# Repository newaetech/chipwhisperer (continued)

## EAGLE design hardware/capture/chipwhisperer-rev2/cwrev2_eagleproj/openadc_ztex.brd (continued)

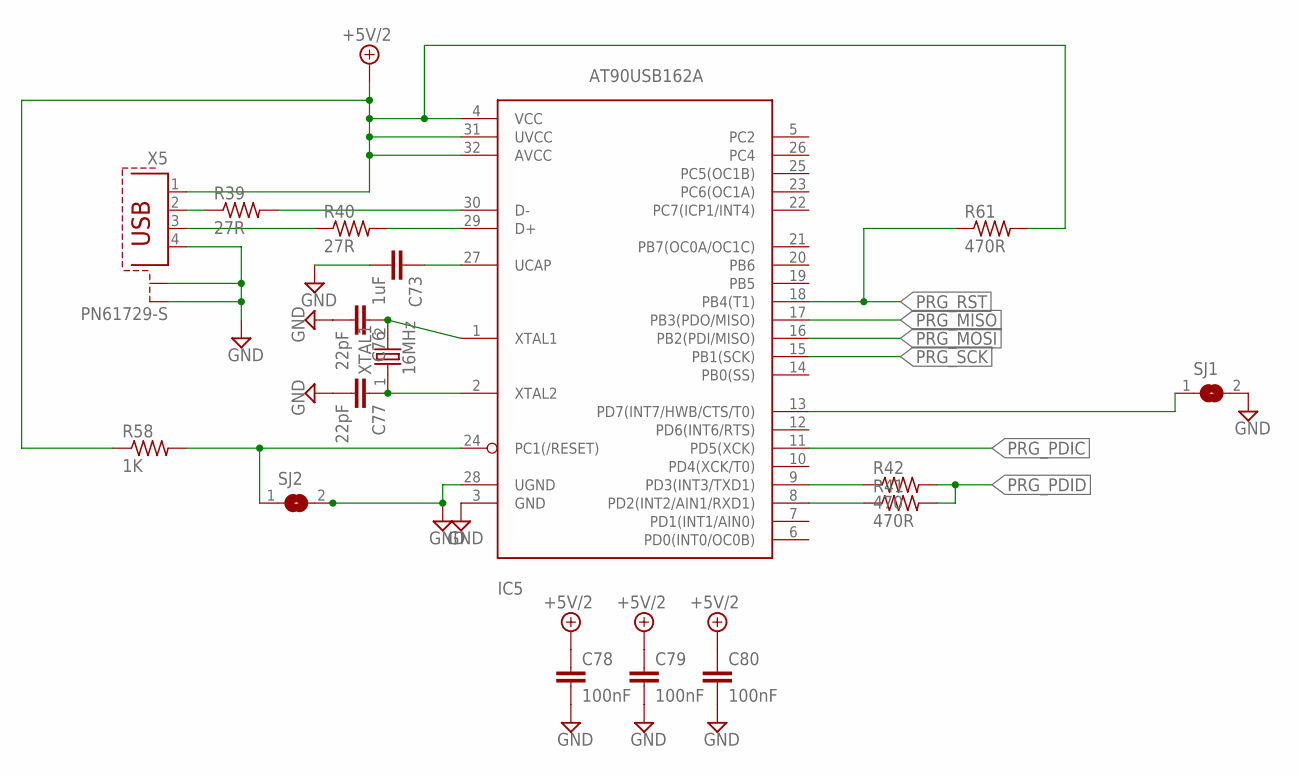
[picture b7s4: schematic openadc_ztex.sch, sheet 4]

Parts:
C73: 1uF; C0603
C76, C77: 22pF; C0603
C78, C79, C80: 100nF; C0603
IC5: AT90USB162A; TQFP32-08
R39, R40: 27R; R0603
R41, R61: 470R; R0603
R42: 470; R0603
R58: 1K; R0603
SJ1, SJ2: SJ
X5: PN61729-S
XTAL1: 16MHz; HC-49U

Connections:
+5V/2: C78.1, C79.1, C80.1, IC5.4 (VCC), IC5.31 (UVCC), IC5.32 (AVCC), R58.1, R61.2, X5.1; also elsewhere on the board
GND: C73.2, C76.2, C77.2, C78.2, C79.2, C80.2, IC5.3 (GND), IC5.28 (UGND), SJ1.2, SJ2.2, X5.4, X5.S1, X5.S2; also elsewhere on the board
unnamed: IC5.30 (D-), R39.2
unnamed: IC5.29 (D+), R40.2
unnamed: R40.1, X5.3
unnamed: R39.1, X5.2
unnamed: IC5.9 (PD3(INT3/TXD1)), R42.1
unnamed: C73.1, IC5.27 (UCAP)
unnamed: IC5.8 (PD2(INT2/AIN1/RXD1)), R41.1
unnamed: C76.1, IC5.1 (XTAL1), XTAL1.2
unnamed: C77.1, IC5.2 (XTAL2), XTAL1.1
unnamed: IC5.13 (PD7(INT7/HWB/CTS/T0)), SJ1.1
unnamed: IC5.24 (PC1(/RESET)), R58.2, SJ2.1
PRG_MISO: IC5.17 (PB3(PDO/MISO)); also elsewhere on the board
PRG_MOSI: IC5.16 (PB2(PDI/MISO)); also elsewhere on the board
PRG_PDIC: IC5.11 (PD5(XCK)); also elsewhere on the board
PRG_PDID: R41.2, R42.2; also elsewhere on the board
PRG_RST: IC5.18 (PB4(T1)), R61.1; also elsewhere on the board
PRG_SCK: IC5.15 (PB1(SCK)); also elsewhere on the board

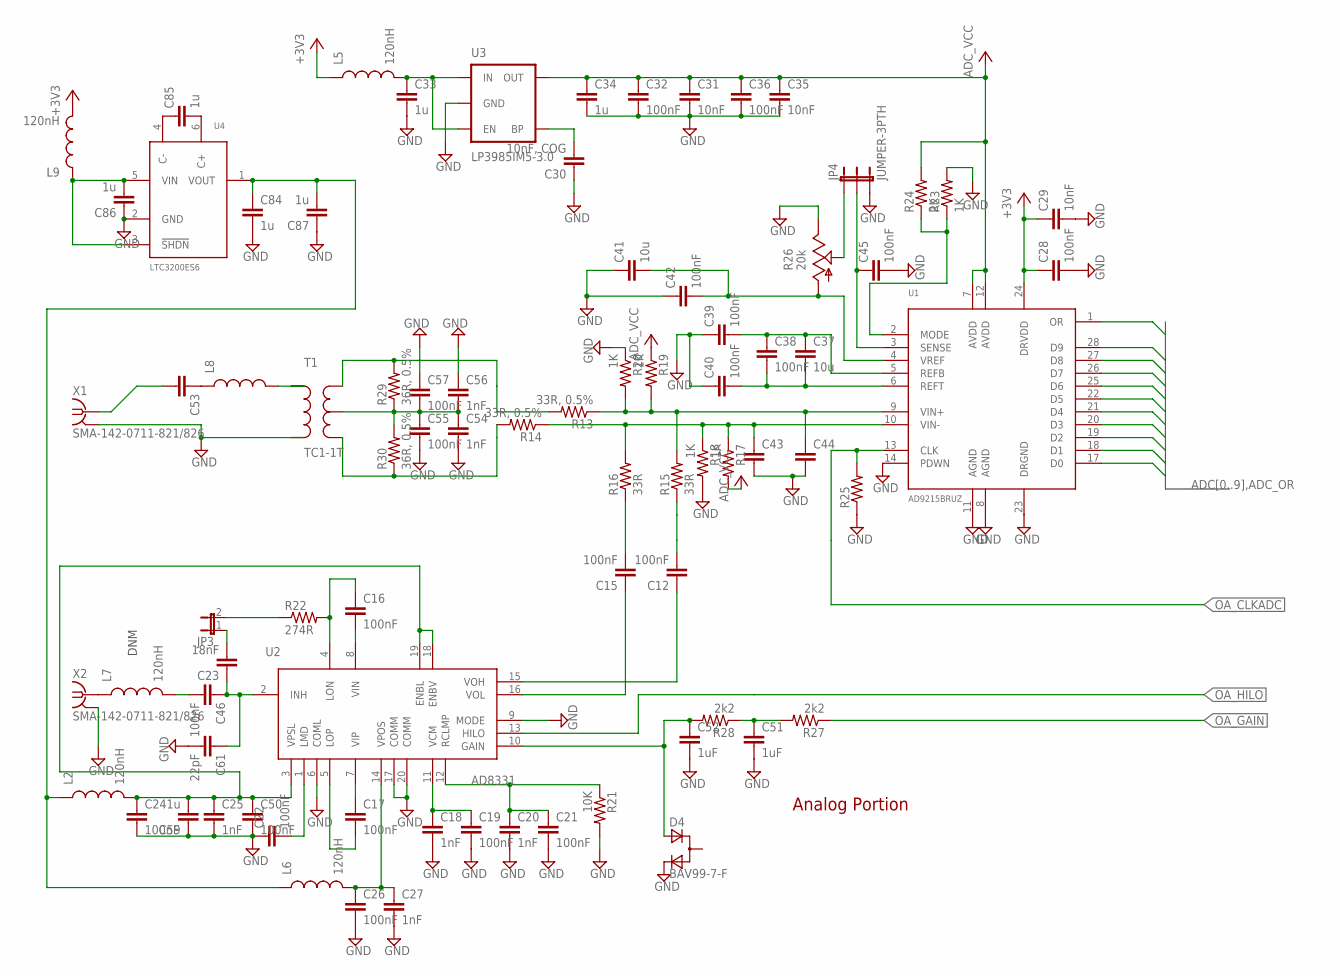
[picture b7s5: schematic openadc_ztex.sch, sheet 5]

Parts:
C12, C15, C46: 100nF; C0603K
C16, C17: 100nF; C0402
C18, C20, C25, C27, C54, C56: 1nF; C0402; PART# C1005X7R1E102K; DIGIKEY# 445-4924-1-ND
C19, C21, C22, C24, C26, C28, C32, C36, C38, C39, C40, C42, C45, C50, C55, C57: 100nF; C0402; PART# GRM155R61A104KA01D; DIGIKEY# 490-1318-1-ND
C23: 18nF; C0603; DIGIKEY# 587-1099-1-ND
C29: 10nF; C0402; DIGIKEY# 490-1312-1-ND
C30: 10nF, COG; C0402; DIGIKEY# 445-2664-1-ND
C31, C35: 10nF; C0402; PART# GRM155R71E103KA01D; DIGIKEY# 490-1312-1-ND
C33, C34, C84, C85, C86, C87: 1u; C0603; PART# GRM188R61A105KA61D; DIGIKEY# 490-1543-1-ND
C37: 10u; C0603; DIGIKEY# C1608X5R0J106K
C41: 10u; C0603
C43, C44: C-EUC0402; C0402
C51, C52: 1uF; C0603
C53: C-EUC0603K; C0603K
C59: 1u; C0402; PART# GRM188R61A105KA61D; DIGIKEY# 490-1543-1-ND
C61: 22pF; C0603; DIGIKEY# 587-1099-1-ND
D4: BAV99-7-F; SOT-23
JP3: JUMPER-2SMD-NC; SJ_2S
JP4: JUMPER-3PTH; 1X03
L2: 120nH; 0603; PART# MLF1608DR12M; DIGIKEY# 445-6234-1-ND
L5, L6, L7, L9: 120nH; 0603
L8: INDUCTOR0603; 0603
R13: 33R, 0.5%; R0603; DIGIKEY# RR08Q33DCT-ND
R14: 33R, 0.5%; R0603
R15, R16: 33R; R0603
R17: 1K; R0402; DIGIKEY# RHM1.00KCDCT-ND
R18, R19, R20, R23: 1K; R0402
R21: 10K; R0603
R22: 274R; R0603; DIGIKEY# RR08P274DCT-ND
R24: 2K; R0603
R25: R-US_R0603; R0603
R26: 20k; 3361P; PART# 3361P-1-203GLF; DIGIKEY# 3361P-203GLFCT-ND
R27, R28: 2k2; R0603
R29, R30: 36R, 0.5%; R0603; DIGIKEY# RR08Q36DCT-ND
T1: TC1-1T; AT224-1A
U1: AD9215BRUZ; TSSOP28; DIGIKEY# AD9215BRUZ-105-ND
U2: AD8331; QSOP20; PART# AD8331ARQZ; DIGIKEY# AD8331ARQZ-ND
U3: LP3985IM5-3.0; SOT23-5; DIGIKEY# LP3985IM5-3.0CT-ND
U4: LTC3200ES6; SOT23-6L
X1, X2: SMA-142-0711-821/826; J502-ND-142-0711-821/826

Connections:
+3V3: C28.1, C29.1, L5.1, L9.2, U1.24 (DRVDD); also elsewhere on the board
ADC_VCC: C31.1, C32.1, C34.1, C35.1, C36.1, R17.2, R19.1, R24.2, U1.7 (AVDD), U1.12 (AVDD), U3.5 (OUT)
GND: C18.2, C19.2, C20.2, C21.2, C22.1, C24.2, C25.2, C26.2, C27.2, C28.2, C29.2, C30.1, C31.2, C32.2, C33.2, C34.2, C35.2, C36.2, C39.1, C40.1, C41.1, C42.1, C43.2, C44.2, C45.2, C50.2, C51.2, C52.2, C54.2, C55.2, C56.1, C57.1, C59.1, C61.2, C84.2, C86.1, C87.1, D4.2 (C), JP4.3, R18.2, R20.1, R21.2, R23.2, R25.1, R26.1 (E), T1.4 (P2), U1.8 (AGND), U1.11 (AGND), U1.14 (PDWN), U1.23 (DRGND), U2.6 (COML), U2.9 (MODE), U2.17 (COMM), U2.20 (COMM), U3.2 (GND), U4.2 (GND), X1.G@1 (2), X1.G@2 (2), X1.G@3 (2), X1.G@4 (2), X2.G@1 (2), X2.G@2 (2), X2.G@3 (2), X2.G@4 (2); also elsewhere on the board
unnamed: C44.1, R13.1, R15.2, R19.2, R20.2, U1.9 (VIN+)
unnamed: C12.2, R15.1
unnamed: C15.2, R16.1
unnamed: C15.1, U2.16 (VOL)
unnamed: C12.1, U2.15 (VOH)
unnamed: C17.2, U2.5 (LOP)
unnamed: C17.1, U2.7 (VIP)
unnamed: C16.2, U2.8 (VIN)
unnamed: C16.1, R22.2, U2.4 (LON)
unnamed: C18.1, C19.1, U2.11 (VCM)
unnamed: C20.1, C21.1, R21.1, U2.12 (RCLMP)
unnamed: C22.2, U2.1 (LMD)
unnamed: C23.1, C46.1, C61.1, U2.2 (INH)
unnamed: C23.2, JP3.1
unnamed: JP3.2, R22.1
unnamed: C26.1, C27.1, L6.2, U2.14 (VPOS)
unnamed: C30.2, U3.4 (BP)
unnamed: C33.1, L5.2, U3.1 (IN), U3.3 (EN)
unnamed: C37.1, C38.1, C39.2, U1.5 (REFB)
unnamed: C37.2, C38.2, C40.2, U1.6 (REFT)
unnamed: C41.2, C42.2, R26.3 (A), U1.4 (VREF)
unnamed: C45.1, JP4.2, U1.3 (SENSE)
unnamed: R23.1, R24.1, U1.2 (MODE)
unnamed: C43.1, R14.1, R16.2, R17.1, R18.1, U1.10 (VIN-)
unnamed: JP4.1, R26.2 (S)
unnamed: L7.1, X2.1
unnamed: C51.1, R27.2, R28.1
unnamed: C52.1, D4.3 (A), R28.2, U2.10 (GAIN)
unnamed: C24.1, C25.1, C50.1, C59.2, L2.2, U2.3 (VPSL), U2.18 (ENBV), U2.19 (ENBL)
unnamed: R14.2, R30.1, T1.3 (S2)
unnamed: C53.2, X1.1
unnamed: C53.1, L8.1
unnamed: L8.2, T1.6 (P1)
unnamed: C85.1, U4.4 (C-)
unnamed: R13.2, R29.2, T1.1 (S1)
unnamed: C54.1, C55.1, C56.2, C57.2, R29.1, R30.2, T1.2 (ST)
unnamed: C46.2, L7.2
unnamed: C85.2, U4.6 (C+)
unnamed: C86.2, L9.1, U4.3 (!SHDN), U4.5 (VIN)
unnamed: C84.1, C87.2, L2.1, L6.1, U4.1 (VOUT)
OA_ADC0: U1.17 (D0); also elsewhere on the board
OA_ADC1: U1.18 (D1); also elsewhere on the board
OA_ADC2: U1.19 (D2); also elsewhere on the board
OA_ADC3: U1.20 (D3); also elsewhere on the board
OA_ADC4: U1.21 (D4); also elsewhere on the board
OA_ADC5: U1.22 (D5); also elsewhere on the board
OA_ADC6: U1.25 (D6); also elsewhere on the board
OA_ADC7: U1.26 (D7); also elsewhere on the board
OA_ADC8: U1.27 (D8); also elsewhere on the board
OA_ADC9: U1.28 (D9); also elsewhere on the board
OA_ADCOR: U1.1 (OR); also elsewhere on the board
OA_CLKADC: R25.2, U1.13 (CLK); also elsewhere on the board
OA_GAIN: R27.1; also elsewhere on the board
OA_HILO: U2.13 (HILO); also elsewhere on the board

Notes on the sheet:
Analog Portion
DNM

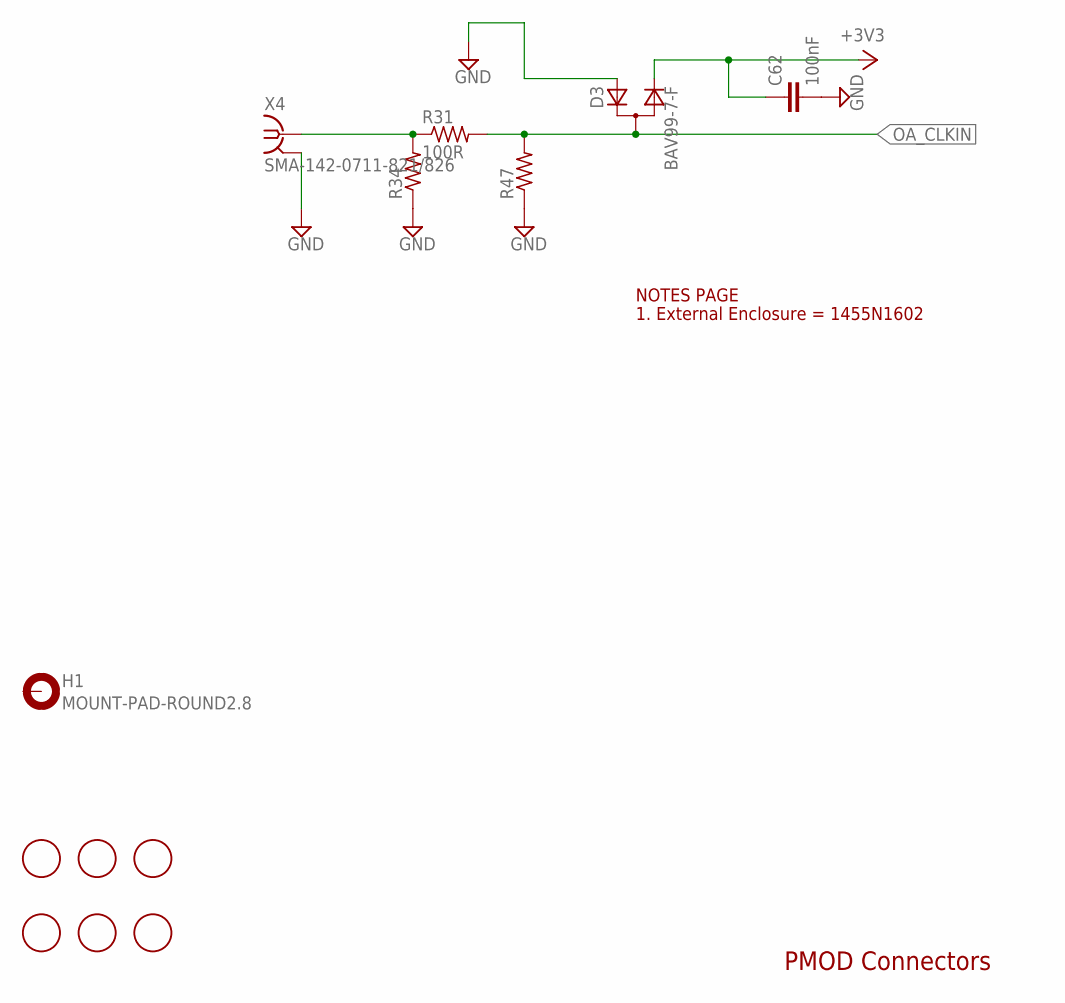
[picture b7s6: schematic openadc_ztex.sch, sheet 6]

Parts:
C62: 100nF; C0603
D3: BAV99-7-F; SOT-23
FID1, FID2, FID3, FID4, FID5, FID6: FIDUCIAL; FIDUCIAL_1MM
H1: MOUNT-PAD-ROUND2.8; 2,8-PAD
R31: 100R; R0805
R34, R47: R-US_R0805; R0805
X4: SMA-142-0711-821/826; J502-ND-142-0711-821/826

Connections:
+3V3: C62.1, D3.2 (C); also elsewhere on the board
GND: C62.2, D3.3 (A), R34.1, R47.1, X4.G@1 (2), X4.G@2 (2), X4.G@3 (2), X4.G@4 (2); also elsewhere on the board
unnamed: R31.1, R34.2, X4.1
OA_CLKIN: D3.1 (CA), R31.2, R47.2; also elsewhere on the board

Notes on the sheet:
PMOD Connectors
NOTES PAGE
1. External Enclosure = 1455N1602

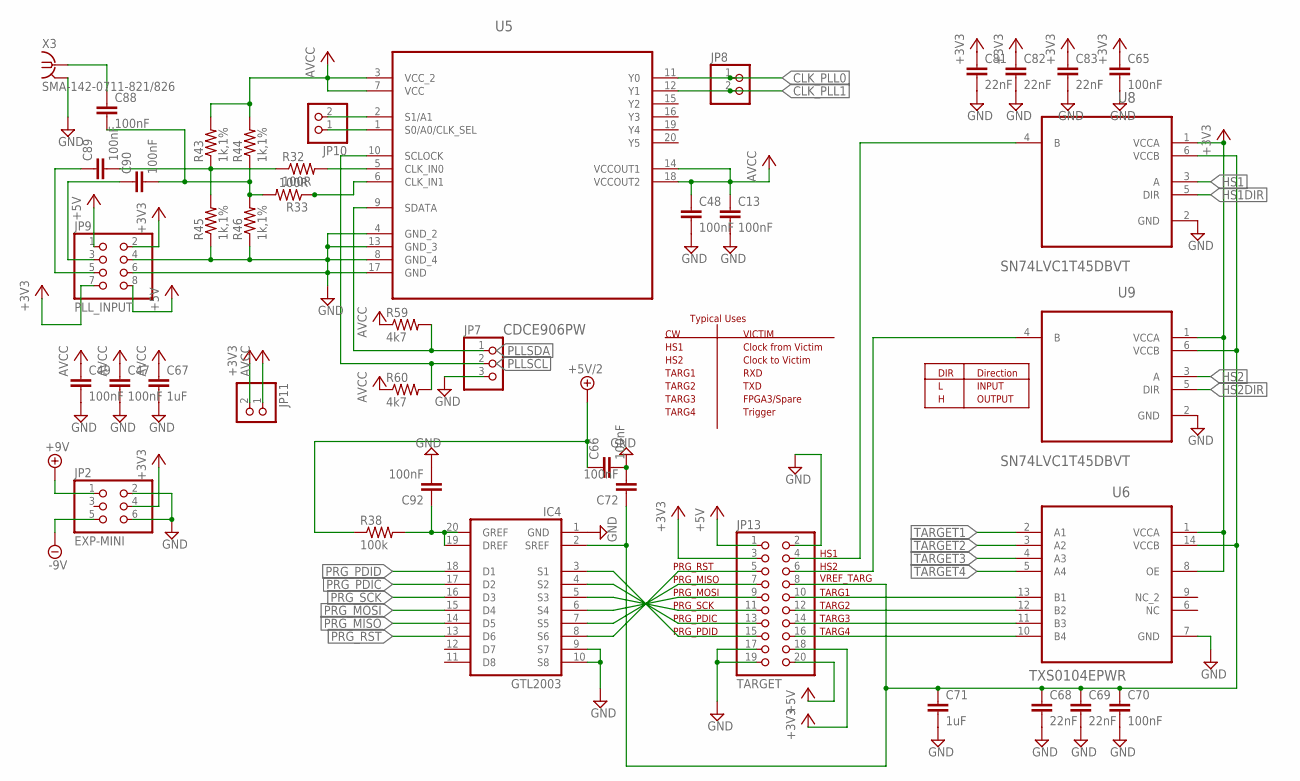
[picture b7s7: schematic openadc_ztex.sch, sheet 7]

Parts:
C13, C47, C48, C49, C65, C66, C70, C72, C88, C89, C90, C92: 100nF; C0603
C67, C71: 1uF; C0603
C68, C69, C81, C82, C83: 22nF; C0603
IC4: GTL2003; TSSOP20
JP2: EXP-MINI; 2X03/90
JP7: PINHD-1X3; 1X03
JP8, JP10, JP11: PINHD-1X2; 1X02
JP9: PLL_INPUT; 2X04/90
JP13: TARGET; 2X10/90
R32, R33: 100R; R0603
R38: 100k; R0603
R43, R44, R45, R46: 1k,1%; R0603
R59, R60: 4k7; R0603
U5: CDCE906PW; SOP65P640X120-20N
U6: TXS0104EPWR; SOP65P640X120-14N
U8, U9: SN74LVC1T45DBVT; SOT95P280X145-6N
X3: SMA-142-0711-821/826; J502-ND-142-0711-821/826

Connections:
+3V3: C65.1, C81.1, C82.1, C83.1, JP2.4, JP9.2, JP9.7, JP11.2, JP13.3, JP13.18, U6.1 (VCCA), U6.8 (OE), U8.1 (VCCA), U9.1 (VCCA); also elsewhere on the board
+5V: JP9.1, JP9.8, JP13.1, JP13.20; also elsewhere on the board
+5V/2: C66.1, R38.1; also elsewhere on the board
+9V: JP2.1; also elsewhere on the board
-9V: JP2.5; also elsewhere on the board
AVCC: C13.1, C47.1, C48.1, C49.1, C67.1, JP11.1, R43.2, R44.2, R59.1, R60.1, U5.3 (VCC_2), U5.7 (VCC), U5.14 (VCCOUT1), U5.18 (VCCOUT2)
CLK_PLL0: JP8.1, U5.11 (Y0); also elsewhere on the board
CLK_PLL1: JP8.2, U5.12 (Y1); also elsewhere on the board
GND: C13.2, C47.2, C48.2, C49.2, C65.2, C66.2, C67.2, C68.2, C69.2, C70.2, C71.2, C72.2, C81.2, C82.2, C83.2, C92.2, IC4.1 (GND), IC4.9 (S7), IC4.10 (S8), JP2.2, JP2.6, JP7.3, JP9.4, JP9.6, JP13.2, JP13.17, JP13.19, R45.1, R46.1, U5.4 (GND_2), U5.8 (GND_4), U5.13 (GND_3), U5.17 (GND), U6.7 (GND), U8.2 (GND), U9.2 (GND), X3.G@1 (2), X3.G@2 (2), X3.G@3 (2), X3.G@4 (2); also elsewhere on the board
HS1: U8.3 (A); also elsewhere on the board
HS1DIR: U8.5 (DIR); also elsewhere on the board
HS2: U9.3 (A); also elsewhere on the board
HS2DIR: U9.5 (DIR); also elsewhere on the board
unnamed: C89.1, JP9.5
unnamed: C90.1, JP9.3
unnamed: C89.2, R32.1, R43.1, R45.2
unnamed: C88.2, C90.2, R33.2, R44.1, R46.2
unnamed: C92.1, IC4.19 (DREF), IC4.20 (GREF), R38.2
unnamed: R33.1, U5.6 (CLK_IN1)
unnamed: IC4.8 (S6), JP13.5
unnamed: JP13.16, U6.10 (B4)
unnamed: JP13.14, U6.11 (B3)
unnamed: JP13.12, U6.12 (B2)
unnamed: JP13.10, U6.13 (B1)
unnamed: C68.1, C69.1, C70.1, C71.1, C72.1, IC4.2 (SREF), JP13.8, U6.14 (VCCB), U8.6 (VCCB), U9.6 (VCCB)
unnamed: IC4.7 (S5), JP13.7
unnamed: IC4.6 (S4), JP13.9
unnamed: IC4.5 (S3), JP13.11
unnamed: IC4.4 (S2), JP13.13
unnamed: IC4.3 (S1), JP13.15
unnamed: JP13.6, U9.4 (B)
unnamed: JP13.4, U8.4 (B)
unnamed: C88.1, X3.1
unnamed: JP10.2, U5.2 (S1/A1)
unnamed: JP10.1, U5.1 (S0/A0/CLK_SEL)
unnamed: R32.2, U5.5 (CLK_IN0)
PLLSCL: JP7.2, R60.2, U5.10 (SCLOCK); also elsewhere on the board
PLLSDA: JP7.1, R59.2, U5.9 (SDATA); also elsewhere on the board
PRG_MISO: IC4.14 (D5); also elsewhere on the board
PRG_MOSI: IC4.15 (D4); also elsewhere on the board
PRG_PDIC: IC4.17 (D2); also elsewhere on the board
PRG_PDID: IC4.18 (D1); also elsewhere on the board
PRG_RST: IC4.13 (D6); also elsewhere on the board
PRG_SCK: IC4.16 (D3); also elsewhere on the board
TARGET1: U6.2 (A1); also elsewhere on the board
TARGET2: U6.3 (A2); also elsewhere on the board
TARGET3: U6.4 (A3); also elsewhere on the board
TARGET4: U6.5 (A4); also elsewhere on the board

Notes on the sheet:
PRG_PDID
PRG_PDIC
PRG_SCK
PRG_MOSI
PRG_MISO
PRG_RST
HS2
HS1
TARG1
TARG2
TARG3
TARG4
VREF_TARG
VICTIM
Clock from Victim
Clock to Victim
RXD
TXD
FPGA3/Spare
Trigger
Typical Uses
DIR
OUTPUT
INPUT
Direction

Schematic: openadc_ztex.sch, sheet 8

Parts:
C91: C-EUC0603; C0603
CON6: USB-FPGA1.15
JP5: PINHD-2X15/90; 2X15/90
R35, R36: 2k2; R0603
U10: ATSHA204-SH; SO08

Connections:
+3V3: C91.1, JP5.3, R35.1, R36.1, U10.8 (VCC); also elsewhere on the board
+5V: JP5.1; also elsewhere on the board
EXPIO5: CON6.A27 (A27~C8~IO_L7N_0), JP5.5
EXPIO6: CON6.B26 (B26~B8~IO_L6P_0), JP5.6
EXPIO7: CON6.A26 (A26~A8~IO_L6N_0), JP5.7
EXPIO8: CON6.A25 (A25~D8~IO_L32N_0), JP5.8
EXPIO9: CON6.B25 (B25~D9~IO_L32P_0), JP5.9
EXPIO10: CON6.E25 (E25~C7~IO_L5P_0), JP5.10
EXPIO11: CON6.A24 (A24~C10~IO_L33N_0), JP5.11
EXPIO12: CON6.B24 (B24~D10~IO_L33P_0), JP5.12
EXPIO13: CON6.E24 (E24~C9~IO_L8P_0), JP5.13
EXPIO14: CON6.E23 (E23~B10~IO_L34P_GCLK19_0), JP5.14
EXPIO15: CON6.E22 (E22~A10~IO_L34N_GCLK18_0), JP5.15
EXPIO16: CON6.E21 (E21~D13~IO_L47P_0_NC45), JP5.16
EXPIO17: CON6.E20 (E20~D12~IO_L47N_0_NC45), JP5.17
EXPIO18: CON6.B20 (B20~F10~IO_L38P_0), JP5.18
EXPIO19: CON6.A20 (A20~C15~IO_L62P_0), JP5.19
EXPIO20: CON6.E19 (E19~A14~IO_L50N_0), JP5.20
EXPIO21: CON6.B19 (B19~D11~IO_L37P_GCLK13_0), JP5.21
EXPIO22: CON6.A19 (A19~C12~IO_L37N_GCLK12_0), JP5.22
EXPIO23: CON6.A18 (A18~C13~IO_L48P_0), JP5.23
EXPIO24: CON6.B18 (B18~A13~IO_L48N_0), JP5.24
EXPIO25: CON6.E18 (E18~B14~IO_L50P_0), JP5.25
EXPIO26: CON6.B17 (B17~C11~IO_L35P_GCLK17_0), JP5.26
EXPIO27: CON6.A17 (A17~A11~IO_L35N_GCLK16_0), JP5.27
EXPIO28: CON6.E17 (E17~A12~IO_L36N_GCLK14_0), JP5.28
GND: C91.2, JP5.2, JP5.4, JP5.29, JP5.30, U10.4 (GND); also elsewhere on the board
HS1: CON6.E14 (E14~B16~IO_L63P_SCP7_0); also elsewhere on the board
HS1DIR: CON6.A15 (A15~C14~IO_L46N_0); also elsewhere on the board
HS2: CON6.A14 (A14~A17~IO_L64N_SCP4_0); also elsewhere on the board
HS2DIR: CON6.B14 (B14~C17~IO_L64P_SCP5_0); also elsewhere on the board
unnamed: CON6.B28 (B28~D6~IO_L3P_0), R36.2, U10.6 (SCL)
unnamed: CON6.A28 (A28~C6~IO_L3N_0), R35.2, U10.5 (SDA)
PLLSCL: CON6.A29 (A29~A5~IO_L2N_0); also elsewhere on the board
PLLSDA: CON6.B29 (B29~C5~IO_L2P_0); also elsewhere on the board
TARGET1: CON6.E13 (E13~C16~IO_L65N_SCP2_0); also elsewhere on the board
TARGET2: CON6.A13 (A13~D17~IO_L65P_SCP3_0); also elsewhere on the board
TARGET3: CON6.B12 (B12~B18~IO_L66P_SCP1_0); also elsewhere on the board
TARGET4: CON6.A12 (A12~A18~IO_L66N_SCP0_0); also elsewhere on the board

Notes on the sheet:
A14
B14
C13
A13
D12
D11
C11
E11

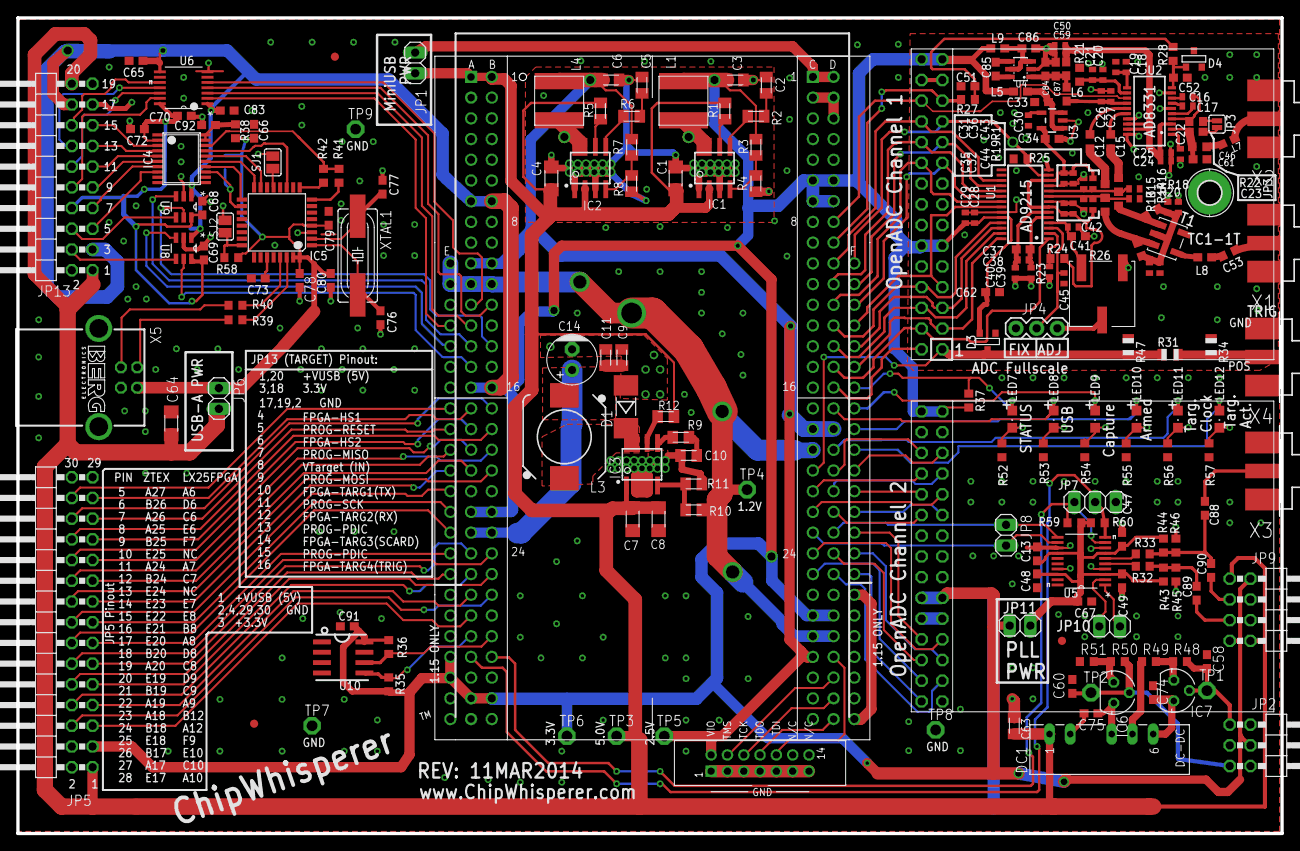
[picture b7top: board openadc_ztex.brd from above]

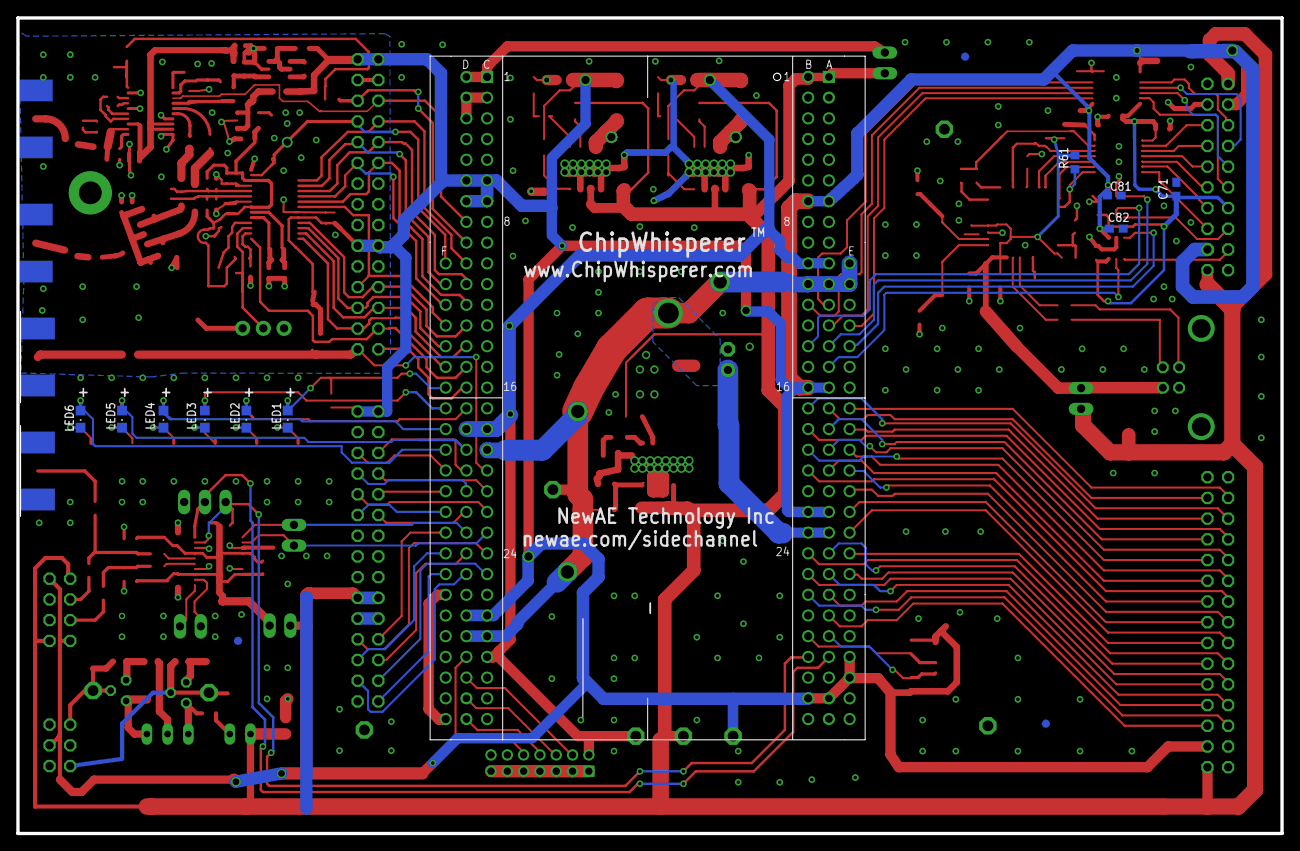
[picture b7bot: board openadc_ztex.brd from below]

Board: 2 copper layers, 155.0 x 100.0 mm, 235 parts (13 on the bottom side), 198 nets.

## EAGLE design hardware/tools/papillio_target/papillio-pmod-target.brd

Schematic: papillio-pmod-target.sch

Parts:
C1, C2, C3, C4, C5, C6, C7, C8: C-EUC0603; C0603
JP1: PINHD-2X6; 2X06
JP2, JP3: PINHD-1X4; 1X04
JP4: PINHD-2X10; 2X10
JP5, JP6: PINHD-2X3; 2X03
U1: TXS0104ED; SOIC127P600X175-14N
U2, U3: SN74LVC1T45DBVT; SOT95P280X145-6N

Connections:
+3V3: C1.1, C2.1, C3.1, C4.1, JP1.11, JP1.12, JP3.3, JP4.3, JP4.18, U1.1 (VCCA), U1.8 (OE), U2.1 (VCCA), U3.1 (VCCA)
+5V: JP3.4, JP4.1, JP4.20
GND: C1.2, C2.2, C3.2, C4.2, C5.2, C6.2, C7.2, C8.2, JP1.9, JP1.10, JP3.1, JP4.2, JP4.17, JP4.19, JP5.6, JP6.6, U1.7 (GND), U2.2 (GND), U3.2 (GND)
unnamed: JP1.2, JP2.1
unnamed: JP1.4, JP2.2, U2.5 (DIR)
unnamed: JP1.6, JP2.3, U3.3 (A)
unnamed: JP1.8, JP2.4, U2.3 (A)
unnamed: JP4.10, U1.10 (B4)
unnamed: JP4.16, U1.13 (B1)
unnamed: JP4.14, U1.12 (B2)
unnamed: JP4.12, U1.11 (B3)
unnamed: JP4.4, U3.4 (B)
unnamed: JP1.1, U1.5 (A4)
unnamed: JP1.3, U1.4 (A3)
unnamed: JP1.5, U1.3 (A2)
unnamed: JP1.7, U1.2 (A1)
unnamed: JP4.6, U2.4 (B)
unnamed: JP4.15, JP6.1
unnamed: JP4.13, JP6.5
unnamed: JP4.5, JP5.5
unnamed: JP4.11, JP5.3
unnamed: JP4.9, JP5.4
unnamed: JP4.7, JP5.1
VCCIO: C5.1, C6.1, C7.1, C8.1, JP4.8, JP5.2, JP6.2, U1.14 (VCCB), U2.6 (VCCB), U3.6 (VCCB)

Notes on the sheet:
PMOD
Papillio Power
TARG1
TARG2
TARG3
TARG4
VCC
MOSI
GND
RST
SCK
MISO
DATA
CLOCK

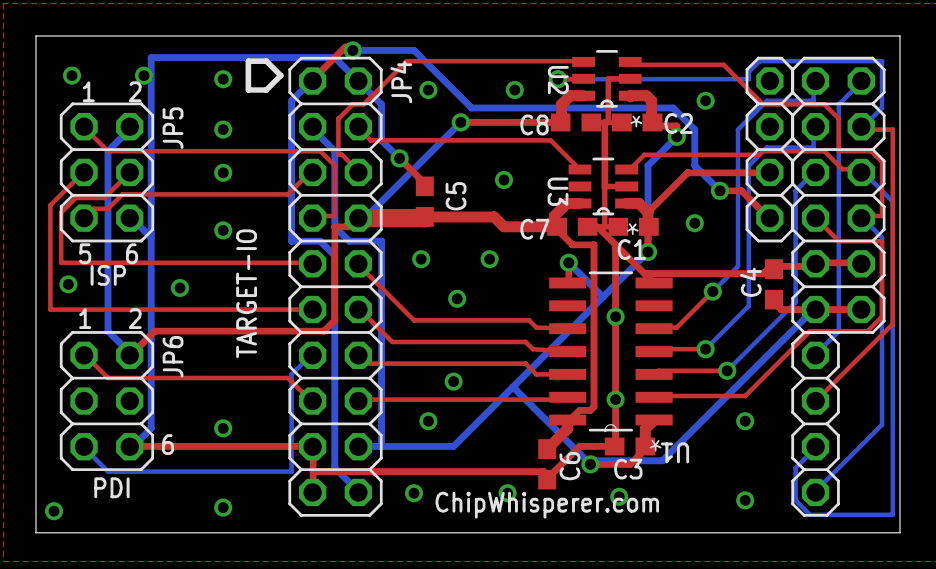
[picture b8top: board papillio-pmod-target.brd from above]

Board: 2 copper layers, 48.0 x 27.6 mm, 17 parts (0 on the bottom side), 24 nets.

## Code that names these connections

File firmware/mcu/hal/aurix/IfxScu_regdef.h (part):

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typedef struct _Ifx_SCU_IOCR_Bits
{
    unsigned int reserved_0:4;              /**< \brief \internal Reserved */
    unsigned int PC0:4;                     /**< \brief [7:4] Control for ESR Pin x (rw) */
    unsigned int reserved_8:4;              /**< \brief \internal Reserved */
    unsigned int PC1:4;                     /**< \brief [15:12] Control for ESR Pin x (rw) */
    unsigned int reserved_16:16;            /**< \brief \internal Reserved */
} Ifx_SCU_IOCR_Bits;

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/** \\brief  ESR Pad Driver Mode Register */
typedef struct _Ifx_SCU_PDR_Bits
{
    unsigned int PD0:3;                     /**< \brief [2:0] Pad Driver Mode for ESR Pins 0 and 1 (rw) */
    unsigned int PL0:1;                     /**< \brief [3:3] Reserved in this product (rw) */
    unsigned int PD1:3;                     /**< \brief [6:4] Pad Driver Mode for ESR Pins 0 and 1 (rw) */
    unsigned int PL1:1;                     /**< \brief [7:7] Reserved in this product (rw) */
    unsigned int reserved_8:24;             /**< \brief \internal Reserved */
} Ifx_SCU_PDR_Bits;
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
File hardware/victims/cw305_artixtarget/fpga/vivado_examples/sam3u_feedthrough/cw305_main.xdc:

######## HARDWARE ON BOARD

#LEDs
set_property DRIVE 8 [get_ports led1]
set_property PACKAGE_PIN T2 [get_ports led1]

set_property DRIVE 8 [get_ports led2]
set_property PACKAGE_PIN T3 [get_ports led2]

set_property DRIVE 8 [get_ports led3]
set_property PACKAGE_PIN T4 [get_ports led3]

#Switch's
set_property PACKAGE_PIN J16 [get_ports j16_sel]
set_property PACKAGE_PIN K16 [get_ports k16_sel]
set_property PACKAGE_PIN L14 [get_ports l14_sel]
set_property PACKAGE_PIN K15 [get_ports k15_sel]
set_property PACKAGE_PIN R1 [get_ports pushbutton]

#PLL Connections
set_property PACKAGE_PIN N13 [get_ports pll_clk1]
#set_property PACKAGE_PIN E12 [get_ports pll_clk2]

######## 20-Pin Connector

set_property PACKAGE_PIN T14 [get_ports tio_trigger_out]

set_property PACKAGE_PIN M16 [get_ports tio_clkout]

set_property PACKAGE_PIN N14 [get_ports tio_clkin]

####### USB Connector: SAM3U interface

set_property PACKAGE_PIN F5 [get_ports usb_clk]

set_property IOSTANDARD LVCMOS33 [get_ports *]
set_property PACKAGE_PIN A7 [get_ports {sam3u_usb_data[0]}]
set_property PACKAGE_PIN B6 [get_ports {sam3u_usb_data[1]}]
set_property PACKAGE_PIN D3 [get_ports {sam3u_usb_data[2]}]
set_property PACKAGE_PIN E3 [get_ports {sam3u_usb_data[3]}]
set_property PACKAGE_PIN F3 [get_ports {sam3u_usb_data[4]}]
set_property PACKAGE_PIN B5 [get_ports {sam3u_usb_data[5]}]
set_property PACKAGE_PIN K1 [get_ports {sam3u_usb_data[6]}]
set_property PACKAGE_PIN K2 [get_ports {sam3u_usb_data[7]}]

set_property PACKAGE_PIN F4 [get_ports {sam3u_usb_addr[0]}]
set_property PACKAGE_PIN G5 [get_ports {sam3u_usb_addr[1]}]
set_property PACKAGE_PIN J1 [get_ports {sam3u_usb_addr[2]}]
set_property PACKAGE_PIN H1 [get_ports {sam3u_usb_addr[3]}]
set_property PACKAGE_PIN H2 [get_ports {sam3u_usb_addr[4]}]
set_property PACKAGE_PIN G1 [get_ports {sam3u_usb_addr[5]}]
set_property PACKAGE_PIN G2 [get_ports {sam3u_usb_addr[6]}]
set_property PACKAGE_PIN F2 [get_ports {sam3u_usb_addr[7]}]
set_property PACKAGE_PIN E1 [get_ports {sam3u_usb_addr[8]}]
set_property PACKAGE_PIN E2 [get_ports {sam3u_usb_addr[9]}]
set_property PACKAGE_PIN D1 [get_ports {sam3u_usb_addr[10]}]

set_property PACKAGE_PIN A4 [get_ports sam3u_usb_rdn]
set_property PACKAGE_PIN C2 [get_ports sam3u_usb_wrn]
set_property PACKAGE_PIN A3 [get_ports sam3u_usb_cen]

#set_property PACKAGE_PIN A5 [get_ports sam3u_usb_trigger]

####### target USB interface (40-pin header, JP3)
# count | header pin # | PCB name  | FPGA pin
# ------+--------------+-----------+---------
#  0    |          5   |       IO5 | A12
#  1    |          6   |       IO6 | B12
#  2    |          7   |       IO7 | A14
#  3    |          8   |       IO8 | A13
#  4    |          9   |       IO9 | A15
#  5    |         10   |      IO10 | B15
#  6    |         11   |      IO11 | C12
#  7    |         12   |      IO12 | C11
#  8    |         13   |      IO13 | B14
#  9    |         14   |      IO14 | C14
# 10    |         15   |      IO15 | B16
# 11    |         16   |      IO16 | C16
# 12    |         17   |      IO17 | C13
# 13    |         18   |      IO18 | D13
# 14    |         23   |      IO23 | D15
# 15    |         24   |      IO24 | D14
# 16    |         25   |      IO25 | E15
# 17    |         26   |      IO26 | D16
# 18    |         27   |      IO27 | E13
# 19    |         28   |      IO28 | E16
# 20    |         29   |      IO29 | F15
# 21    |         30   |      IO30 | F12
# 22    |         31   |      IO31 | E11
# 23    |         32   |      IO32 | F13
# ------+--------------+-----------+---------
# 24    |         33   |      TIO4 | T14
# 25    |         34   |    EMCCLK | M15
# 26    |         37   |     IOD_P | H16
# 27    |         38   |     IOD_N | G16

# physical arrangement:
# header pin # | PCB name  | FPGA pin | header pin # | PCB name  | FPGA pin | 
# -------------+-----------+----------+--------------+-----------+----------+-
#          5   |       IO5 | A12      |          6   |       IO6 | B12      |
#          7   |       IO7 | A14      |          8   |       IO8 | A13      |
#          9   |       IO9 | A15      |         10   |      IO10 | B15      |
#         11   |      IO11 | C12      |         12   |      IO12 | C11      |
#         13   |      IO13 | B14      |         14   |      IO14 | C14      |
#         15   |      IO15 | B16      |         16   |      IO16 | C16      |
#         17   |      IO17 | C13      |         18   |      IO18 | D13      |
# -------------+-----------+----------+--------------+-----------+----------+-
#         NC   |        NC | NC       |         NC   |        NC | NC       | 
#         NC   |        NC | NC       |         NC   |        NC | NC       | 
# -------------+-----------+----------+--------------+-----------+----------+-
#         23   |      IO23 | D15      |         24   |      IO24 | D14      |
#         25   |      IO25 | E15      |         26   |      IO26 | D16      |
#         27   |      IO27 | E13      |         28   |      IO28 | E16      |
#         29   |      IO29 | F15      |         30   |      IO30 | F12      |
#         31   |      IO31 | E11      |         32   |      IO32 | F13      |
# -------------+-----------+----------+--------------+-----------+----------+-


# to Genesys2 JB:
set_property PACKAGE_PIN A12 [get_ports {ext_usb_data[3]}]
set_property PACKAGE_PIN A14 [get_ports {ext_usb_data[2]}]
set_property PACKAGE_PIN A15 [get_ports {ext_usb_data[1]}]
set_property PACKAGE_PIN C12 [get_ports {ext_usb_data[0]}]

set_property PACKAGE_PIN B12 [get_ports {ext_usb_data[7]}]
set_property PACKAGE_PIN A13 [get_ports {ext_usb_data[6]}]
set_property PACKAGE_PIN B15 [get_ports {ext_usb_data[5]}]
set_property PACKAGE_PIN C11 [get_ports {ext_usb_data[4]}]

# to Genesys2 JA:
set_property PACKAGE_PIN D15 [get_ports {ext_usb_wrn }]
set_property PACKAGE_PIN E15 [get_ports {ext_usb_rdn }]
set_property PACKAGE_PIN E13 [get_ports {ext_usb_cen }]
set_property PACKAGE_PIN F15 [get_ports {ext_usb_clk }]

set_property PACKAGE_PIN D14 [get_ports {ext_usb_addr[10]}]
set_property PACKAGE_PIN D16 [get_ports {ext_usb_addr[9]}]
set_property PACKAGE_PIN E16 [get_ports {ext_usb_addr[8]}]
set_property PACKAGE_PIN F12 [get_ports {ext_usb_addr[7]}]

# between JA/JB, to Genesys2 JC:
set_property PACKAGE_PIN B14 [get_ports {ext_usb_addr[0]}]; # white
set_property PACKAGE_PIN B16 [get_ports {ext_usb_addr[1]}]; # red
set_property PACKAGE_PIN C13 [get_ports {ext_usb_addr[2]}]; # yellow

set_property PACKAGE_PIN C14 [get_ports {ext_usb_addr[3]}]; # black
set_property PACKAGE_PIN C16 [get_ports {ext_usb_addr[4]}]; # green
set_property PACKAGE_PIN D13 [get_ports {ext_usb_addr[5]}]; # blue

set_property PACKAGE_PIN E11 [get_ports {ext_usb_addr[6]}];      # white
set_property PACKAGE_PIN F13 [get_ports {ext_tio_trigger_in}];   # yellow


create_clock -period 10.000 -name usb_clk -waveform {0.000 5.000} [get_nets usb_clk]
create_clock -period 10.000 -name tio_clkin -waveform {0.000 5.000} [get_nets tio_clkin]
create_clock -period 10.000 -name pll_clk1 -waveform {0.000 5.000} [get_nets pll_clk1]

# both input clocks have same properties so there is no point in doing timing analysis for both:
set_case_analysis 1 [get_pins U_clocks/CCLK_MUX/S]

# No spec for these, seems sensible:
set_input_delay -clock usb_clk -add_delay 2.000 [get_ports sam3u_usb_addr]
set_input_delay -clock usb_clk -add_delay 2.000 [get_ports sam3u_usb_data]
#set_input_delay -clock usb_clk -add_delay 2.000 [get_ports sam3u_usb_trigger]
set_input_delay -clock usb_clk -add_delay 2.000 [get_ports sam3u_usb_cen]
set_input_delay -clock usb_clk -add_delay 2.000 [get_ports sam3u_usb_rdn]
set_input_delay -clock usb_clk -add_delay 2.000 [get_ports sam3u_usb_wrn]

set_input_delay -clock usb_clk -add_delay 0.000 [get_ports j16_sel]
set_input_delay -clock usb_clk -add_delay 0.000 [get_ports k16_sel]
set_input_delay -clock [get_clocks usb_clk] -add_delay 0.500 [get_ports pushbutton]

set_output_delay -clock usb_clk 0.000 [get_ports led1]
set_output_delay -clock usb_clk 0.000 [get_ports led2]
set_output_delay -clock usb_clk 0.000 [get_ports led3]
set_output_delay -clock usb_clk 0.000 [get_ports sam3u_usb_data]
set_output_delay -clock usb_clk 0.000 [get_ports tio_trigger_out]
set_output_delay -clock usb_clk 0.000 [get_ports tio_clkout]
set_false_path -to [get_ports led1]
set_false_path -to [get_ports led2]
set_false_path -to [get_ports led3]
set_false_path -to [get_ports sam3u_usb_data]
set_false_path -to [get_ports tio_trigger_out]
set_false_path -to [get_ports tio_clkout]

set_property CFGBVS VCCO [current_design]
set_property CONFIG_VOLTAGE 3.3 [current_design]

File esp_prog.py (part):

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scope = cw.scope()
scope.default_setup()
target = cw.target(scope)
scope.io.tio3 = 0
scope.io.pdic=0
scope.clock.clkgen_freq = 26E6
import time
scope.io.nrst = 0
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MAX_UINT24 = 0xffffff

DEFAULT_TIMEOUT = 3                   # timeout for most flash operations
START_FLASH_TIMEOUT = 20              # timeout for starting flash (may perform erase)
CHIP_ERASE_TIMEOUT = 120              # timeout for full chip erase
MAX_TIMEOUT = CHIP_ERASE_TIMEOUT * 2  # longest any command can run
SYNC_TIMEOUT = 0.1                    # timeout for syncing with bootloader
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
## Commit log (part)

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2023-07-13 CW340: add docstrings and jumper warning.
2023-07-13 appease mypy
2023-07-27 Husky triggering updates.
    1. Allow SAD to generate triggers when not armed (i.e. after the ADC
    capture is done).
    2. Retrieve timestamped trigger times (when using multiple triggers).
2023-07-27 Husky: automatically set ADC high/low speed mode.
    Previously it was always set to low speed mode; the datasheet recommends
    high speed mode when the sampling frequency is > 80 MHz; this is what we
    do now.
2023-07-27 Arm RSA WIP changes
2023-07-28 Update Husky FPGA bitfile: fix for https://github.com/newaetech/chipwhisperer-husky-fpga/issues/16
2023-08-01 revert back to original rsa arm code
2023-08-15 FPGA targets: move ss2 wrapper to fpga-common.
2023-08-15 Add SS2-style iCE40 AES FPGA target.
    This allows iCE40 to be treated as a pseudo-CW305 target (see CW305 AES
    notebook).
2023-08-15 update mac install instructions
2023-08-17 CW310: fix typo on current_vccint property
2023-08-17 Allow CW310/340 to use all CW305 properties.
2023-08-17 Add ext_offset[x] = y support for multiglitch
2023-08-17 remove print from MultiGlitchList
2023-08-22 Remove windows install section about make/compilers (always installed now)
2023-08-23 Update jupyter submodule
2023-08-26 Refactored vcc glitch mosfet control; Refactored default and glitch setup/disable API; Added message utilities; Added optimized data copy; Added API utilities and tests
2023-08-28 Add sequenced triggers for Husky.
2023-08-28 Husky USERIO: print info about each pin.
2023-08-28 make mypy happy
2023-08-29 Husky: expand num_triggers property.
2023-08-30 Tweaks towards supporting > 2 sequence triggers.
2023-09-01 Husky trig seq: option to make SAD always active.
2023-09-01 Husky: tweak USERIO fpga_mode signals
2023-09-05 test_husky.py: make test_pll smarter
2023-09-05 update virtual box instructions for potential USB issue
2023-09-05 Add target FW for trace-less uecc attack notebook.
2023-09-06 Update jupyter for uecc notebooks.
2023-09-06 Update Husky FPGA bitfile.
    Adds trigger timestamp and trigger sequencer features. Bitfile built
    from:
    https://github.com/newaetech/chipwhisperer-husky-fpga/commit/71dec210372a61f6cb1d9f99b23cbf440d9396ae
2023-09-06 Make sure np arrays used for clock calcs are int64
2023-09-10 Optimized GlitchController iterator and added utilites; Added glitch looper API; Added Simple Serial glitch looper test script
2023-09-12 add custom-firmware.rst
2023-09-12 Update side bar
2023-09-14 Don't check stm32fprog pins on Nano
2023-09-15 fix missing newline in docs
2023-09-15 Fix lite build
2023-09-20 Add usart capability to CW340
2023-09-21 Add multi usart to CW310/CW340
2023-09-25 Update Husky bitfiles, test script.
    Adds trigger sequencer.
2023-09-26 Husky: make default_setup() reset segments to 1
2023-10-01 Refactored GPIO API
2023-10-04 Fix https://github.com/newaetech/chipwhisperer/issues/463
2023-10-06 Add USART dependency for CW310
    The CW310 target currently is missing the USART dependency. This
    PR fixes the issue.
2023-10-09 [naeusb] Remove claimInterface
    Remove `self.handle.claimInterface(0)` to enable connection for CW305.
2023-10-10 Add getCWType to cw340
2023-10-12 Add missing properties to CW310.py
2023-10-16 Husky: fix https://github.com/newaetech/chipwhisperer-husky-fpga/issues/17 and add more testing around it.
2023-10-24 Allow to connect to Nano by name.
    (when multiple ChipWhisperers are connected)
2023-10-24 Fix missing arg in husky clock debug msg
2023-10-27 add nbstripout to install instructions
2023-10-31 Remove old FPGA target material.
2023-10-31 (re)-add fpga-common submodule
2023-10-31 Target FPGA: remove duplicate source files.
2023-11-01 Target FPGA: update generate_firmware_files.py
    (pull target FPGA bitfiles from their new locations)
2023-11-02 Jupyter update (sca204, Ibex)
2023-11-02 Add RTFM links to FPGA targets README.
2023-11-03 typo
2023-11-06 Documentation fixes.
2023-11-06 Fix footguns around hidden Husky stream properties
2023-11-14 Claim interface on Darwin
2023-11-19 FPGA register updates.
    Functionally equivalent. FPGA register address space was getting tight
    and so some were combined or eliminated. FPGA-side changes are:
    https://github.com/newaetech/chipwhisperer-husky-fpga/commit/7e0bec0497cc4ab0be0edc18e0264e9167e5a83e
2023-11-23 Husky: add "trigger too soon" error.
2023-11-23 FPGA targets: fix AES defines file.
    Name/location were wrong, due to recent target FPGA organizational
    changes.
2023-11-27 Make bits_per_sample Husky-only.
2024-01-02 Bump tj-actions/changed-files in /.github/workflows
    Bumps [tj-actions/changed-files](https://github.com/tj-actions/changed-files) from 29.0.1 to 41.0.0.
    - [Release notes](https://github.com/tj-actions/changed-files/releases)
    - [Changelog](https://github.com/tj-actions/changed-files/blob/main/HISTORY.md)
    - [Commits](https://github.com/tj-actions/changed-files/compare/v29.0.1...v41.0.0)
    ---
    updated-dependencies:
2024-01-15 Husky: update bitfile.
    From https://github.com/newaetech/chipwhisperer-husky-fpga/commit/e410ae83b16c6dcdb642a2ace36b3b21f1b53098
2024-02-02 Add glitch_plot_3d() for 3D plots
2024-02-24 Added reset of the scope's connection before closing it
2024-03-18 Update stm32f0_hal_nano.c
    Add functions led_ok_on() led_ok_off() led_error_on() and led_error_off() to be abe to control target leds from firmware
2024-03-19 Fix led_ok and led_error being ifdef'd out
2024-03-20 Fix typo? in scope-api
2024-03-20 Fix tracewhisperer docs
2024-03-30 make BAUD_RATE definable
2024-03-30 remove FOSC defines, make everything based on F_CPU
2024-03-30 fix cpu rate checking
2024-03-30 fix readme
2024-03-30 fix delay
2024-04-07 update documentation on target_pwr (disables some IO)
2024-04-11 Husky SAD updates WIP.
2024-04-15 Add xonxoff support
2024-04-15 Fix version for XONXOFF for CW310
2024-04-16 Make test_s6_glitch.py run again.
    WIP as current usefulness is low.
2024-04-17 Fix test_s6.py test script.
    Renamed from test_s6_glitch.py, because it now does more than glitch
    testing: it also checks the CW generated clock.
2024-04-17 Update Husky bitfile for https://github.com/newaetech/chipwhisperer/issues/481
2024-04-17 Remove double glitch warning.
    Well tested by tests/test_s6.py; confident that double glitches are no
    longer a thing.
2024-04-23 Add **kwargs to CDC
2024-04-23 Add XMEGA16D4 programming
2024-05-30 Add scope.glitch.mmcm_locked property Lite/Pro.
2024-05-31 Add parity and stopbits for serial
2024-06-18 glitch controller plot fixes, allow saving and loading of results
2024-06-25 Husky: have userio.drive_data return what was set.
2024-06-27 Fix for make 4.4+?
2024-07-15 Husky SAD: make reference setter friendlier.
    Accept more types as-is and translate as needed instead of requiring
    user to do so.
2024-08-08 Husky: fix scope.adc.errors reporting.
    'trigger too soon' and 'gain too low' were switched.
2024-08-09 Husky SAD: more error checking.
2024-08-13 Add delay to default_setup() for clocks to settle.
    On CW-lite, calling default_setup() after connecting caused
    scope.clock.adc_freq to read and cache the clock frequency before it's
    settled (even if scope.clock.adc_locked is True). A small delay seems
    like the best fix.
2024-08-13 move mcu firmware to firmware/mcu
2024-08-14 remove hardware/capture and common
2024-08-14 remove artix target
2024-08-14 Remove cw308 main files
2024-08-14 remove final hardware files
2024-08-14 Husky SAD: add unblock for writing reference.
    With new implementations, this is needed after an unsuccessful capture.
2024-08-14 Change readthedocs to use pip
2024-08-15 Add SAD explorer and model classes.
2024-08-15 Husky: fix times reported by get_trigger_times()
    They were 2 cycles short.
2024-08-16 SAD explorer: improve layout
2024-08-16 SAD explorer: clear capture_trace() output
2024-08-20 SAD model: small improvements (for demo).
2024-08-20 SAD explorer: various improvements.
2024-08-22 Husky SAD: make trigger_sample functional.
2024-08-22 SAD explorer improvements.
    Add the trigger_sample property;
    do some sanity checking of the capture parameters before going ahead.
2024-08-22 SAD explorer improvements.
    - make enabled_samples functional
    - add extra_presamples feature
    - account for trigger_sample in calc_sad()
2024-08-23 SAD explorer improvements.
    - execute excluded samples *before* the trace capture!
    - put everything under 'with captureout'
2024-08-23 Husky SAD: cleanup.
2024-08-29 Husky: don't arm if XADC error disables trigger.
    XADC error shuts down MMCMs and SAD; the blinking red lights may not be
    enough (guilty as charged), so explicitely alert user that trying to
    capture is pointless.
2024-08-30 Husky SAD demo notebook.
2024-08-30 Update Husky SAD demo notebook.
2024-08-30 Re-add pre-compiled FW that got lost in the move.
    (these are needed for SAD and trace tests where re-compiling risks
    needed to tweak capture parameters)
2024-08-31 Update LICENSE.txt
    Default to apache2 (doesn't override anything else, some files are GPL still)
2024-09-16 Add more typing, WIP husky plus stuff
2024-09-20 Jupyter updates (bokeh 3.x).
2024-09-23 SAD explorer: workaround ipywidgets bug.
    Using Textarea() instead of Text() as per https://github.com/jupyter-widgets/ipywidgets/issues/3915
2024-09-24 Husky SAD: reference setting bugfix.
    Fix reference setting when providing a shortened reference.
2024-10-03 Update debugging docs to make hackyness clear
2024-10-15 Jupyter updates.
2024-10-22 Big update to PLL programming.
    Updates all PLL registers, in the prescribed order, whenever any of them
    needs to be updated. Towards fixing
    https://github.com/newaetech/chipwhisperer/issues/490.
    Functional (but not fully tested) for XIN case; not tested at all with
    external clock.
2024-10-24 Husky: change scope.clock.adc_phase dimensions.
    Now expressed in percentage of the ADC clock period (instead of [-255,
    255]). More user-friendly since the phase step size is variable (and can
    now be accessed via adc_phase_step_size).
2025-04-30 Removed unneeded /
    Removed unneeded / in HALPATH and HALBASE
2025-05-07 Simplify base firmware
2025-05-12 Small documentation fixes
    Mostly spelling/capitalization, a few small formatting changes also. Almost all changes are in documentation/code comments
2025-05-14 stm32f3 enable clock cycle count [Details]
    The starting point are these KWs: SysTick, SysTick_Handler, SystemInit, sysclk
    Notice that
    arm_math.h ← arm_const_struct.h
    and core_cm{7,4,3,0,0plus}.h contains SysTick_Config, the same code as that in
    SystemInit in mps2_halc, which will enable clock cycle count, so include
    arm_math.h at the beginning.
2025-05-15 Update flash_sam4s.ld
    Bugfix, set ram to 160KB instead of 65KB
2025-05-15 Starting on documentation for NAEUSB_Backend
2025-05-15 Finished documentation and type hints for NAEUSB_Backend class
2025-05-15 Forgot one
2025-05-16 Fixed lint errors
2025-05-19 Added to and cleaned up some documentation for functions in __init__.py
2025-05-19 Maybe this will work for .gitignore
2025-05-19 Spaces in sam3update docstring
2025-06-10 WIP changes
2025-06-10 Additional trace changes
2025-06-11 Update gitmodules
2025-06-17 Update SimpleSerial2.py
    reenable `str(target)`
2025-07-07 Changes for new project
2025-07-11 MAGMA firmware
2025-07-15 made changes to magma
2025-07-24 update caputre_trace() for new project, import new project
2025-07-24 project updates
2025-07-24 Fix ktp iterator
2025-07-24 Default to traces as int16
2025-07-24 Reduce number of imports
2025-08-07 Almost done CPA
2025-09-25 Husky: tweak ADS4128 clock edge timing.
    For better sampling at high clock frequencies.
2025-10-20 Change return values of project fields
2025-11-14 Add TPIU pure-python parser
    Orbuculum stopped accepting raw TPIU frames since v2.2.0.
    As TPIU framing is stable, parsing it in Python makes sense, leaving the
    other more complicated layers to Orbuculum.
    The code additionnaly leveraged the official python wrapper pyorb
    (`pip install python-orbuculum`) to directly use liborb and thus removes
    the need to write data to files, call binaries and then parse their text
2025-11-14 Ask mypy to ignore pyorb as it is not typed
2025-12-09 Fix typo
2026-01-28 Fix NEORV32 programmer for updated bootloader behavior
